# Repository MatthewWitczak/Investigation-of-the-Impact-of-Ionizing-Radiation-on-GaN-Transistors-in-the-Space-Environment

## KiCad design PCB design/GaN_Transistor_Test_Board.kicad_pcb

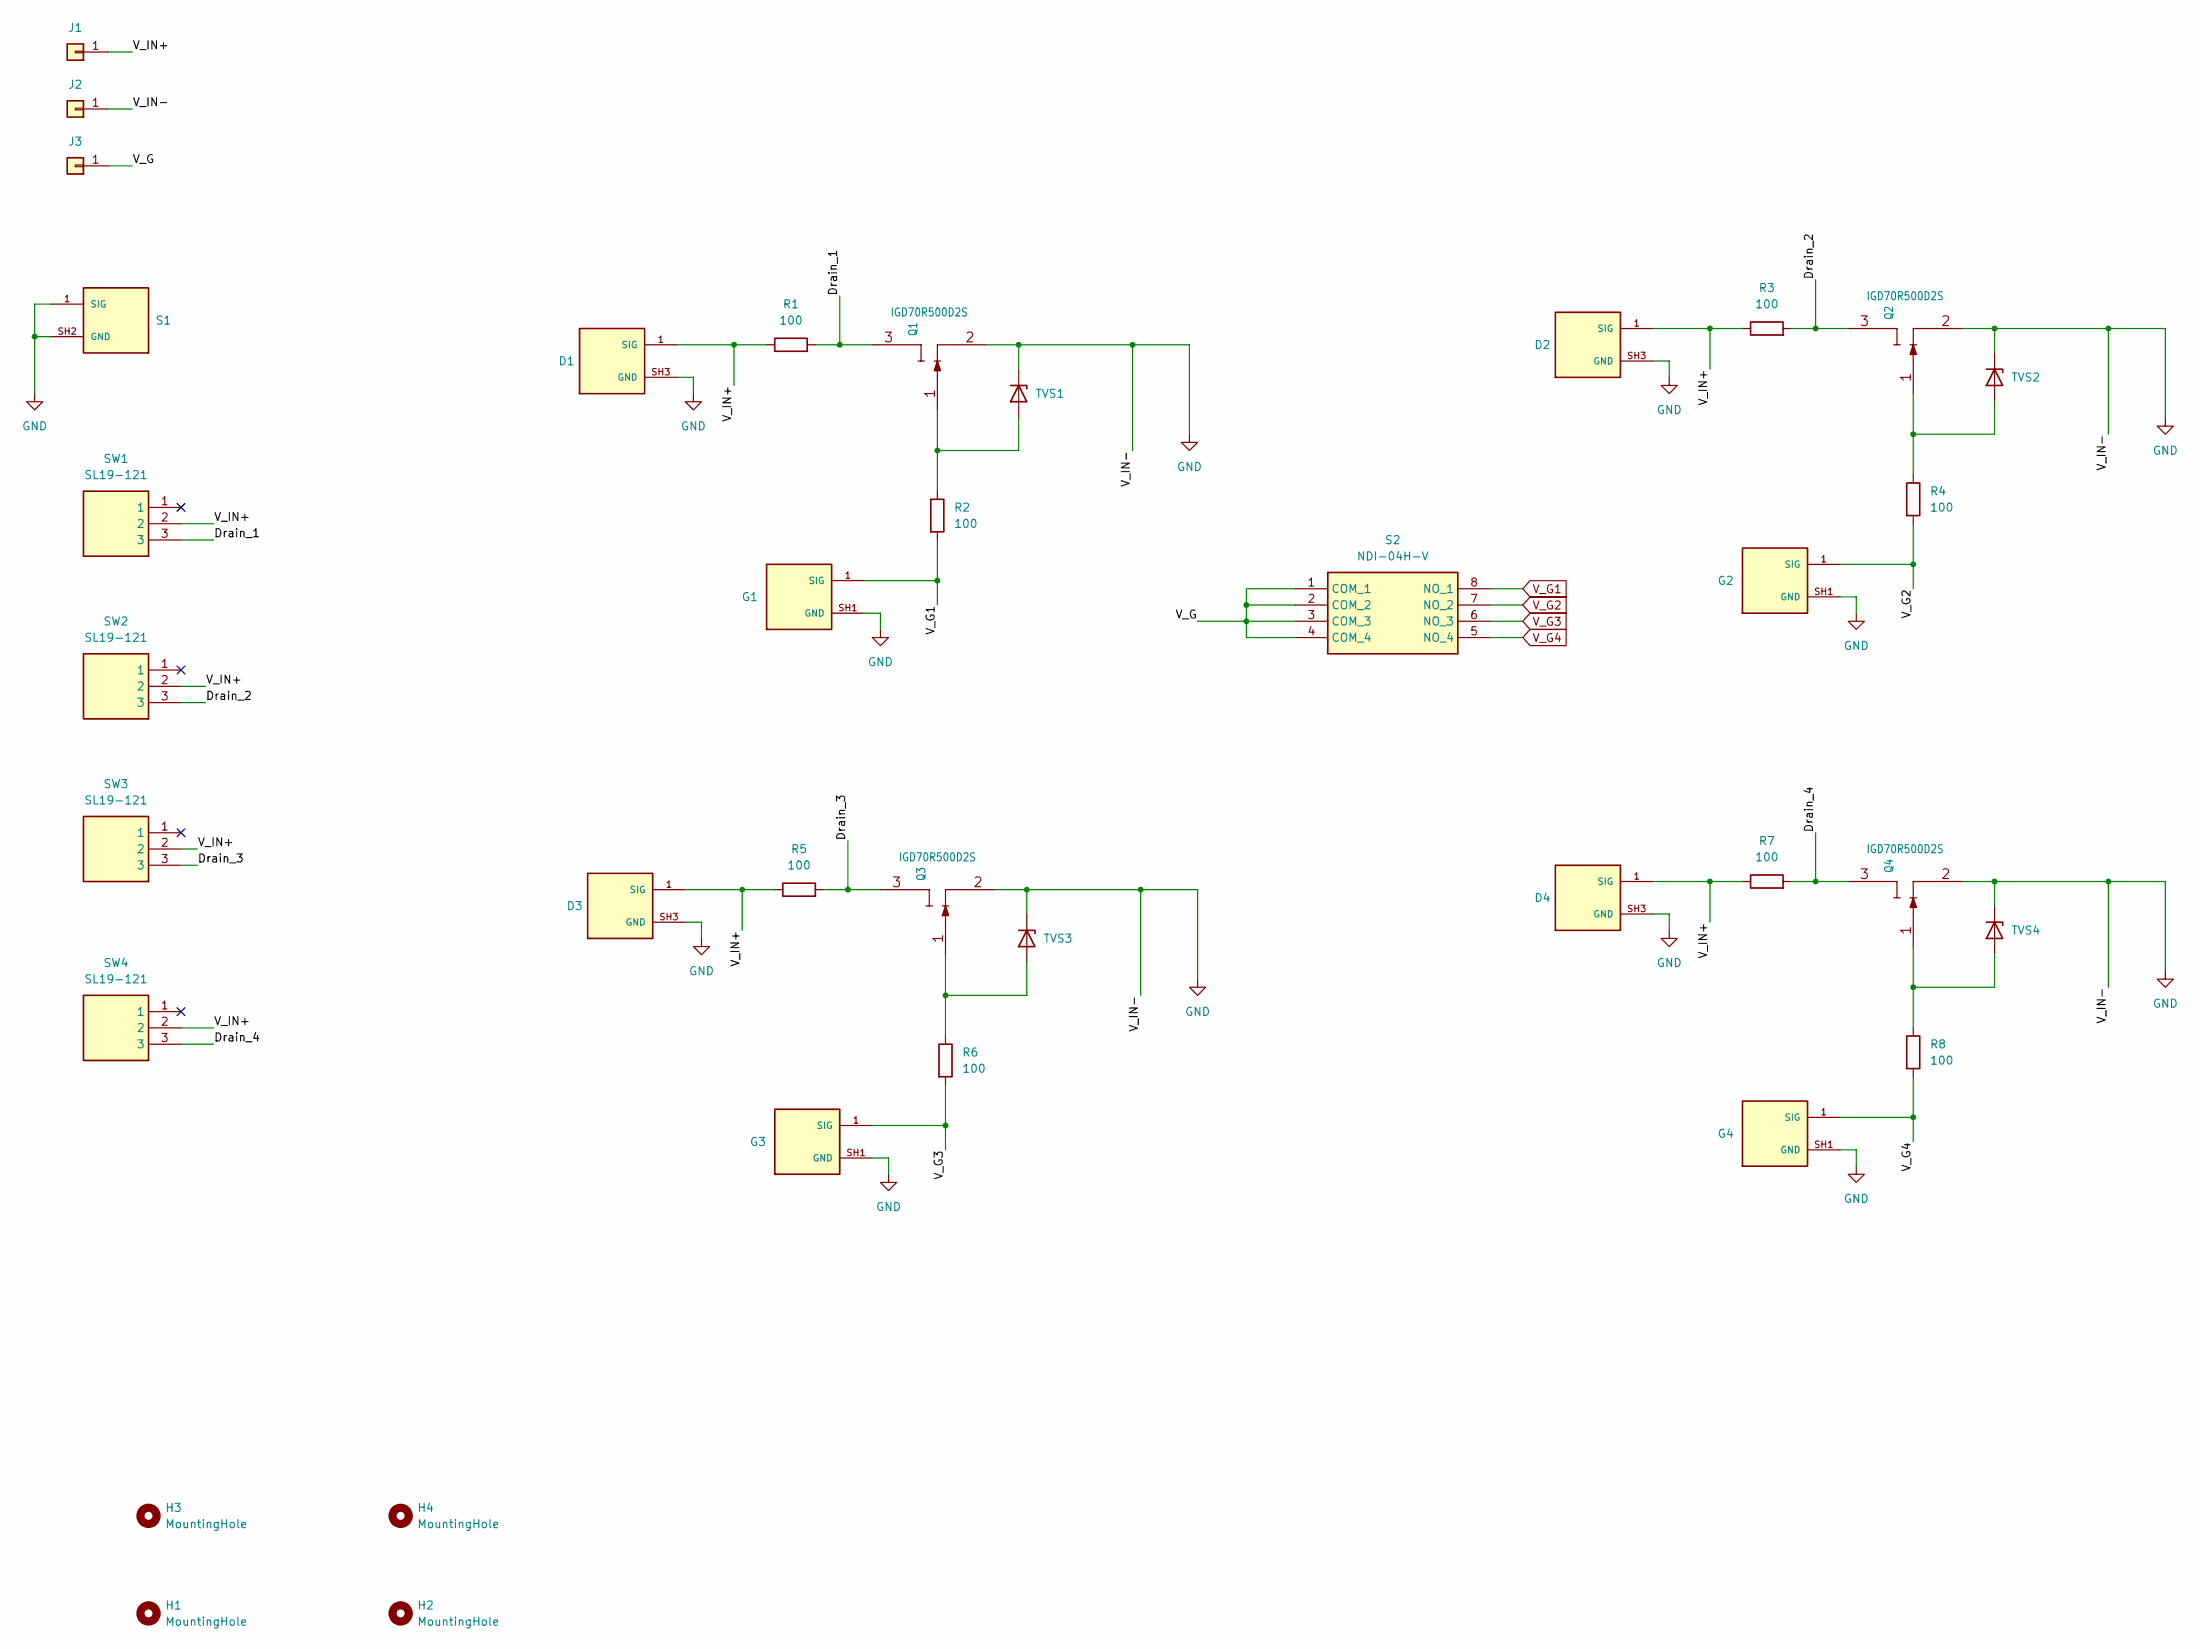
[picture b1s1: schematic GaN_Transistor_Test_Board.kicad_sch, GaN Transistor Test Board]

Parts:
D1, D2, D3, D4: 1-1337445-0; TE_1-1337445-0; PARTREV C
G1, G2, G3, G4: 1-1337445-0; TE_1-1337445-0; PARTREV C
H1, H2, H3, H4: MountingHole; MountingHole_4.3mm_M4
J1, J2, J3: Conn_01x01; CONN1_FCR7350R_CLF
Q1, Q2, Q3, Q4: IGD70R500D2S; IFX-PG-TO252-3N-37-V1
R1, R3, R5, R7: 100; R_LOAD
R2, R4, R6, R8: 100; R_1206_3216Metric_Pad1.30x1.75mm_HandSolder
S1: 1-1337445-0; TE_1-1337445-0; PARTREV C
S2: NDI-04H-V; NDI04HV; Manufacturer_Part_Number NDI-04H-V
SW1, SW2, SW3, SW4: SL19-121; SL19121; Manufacturer_Part_Number SL19-121
TVS1, TVS2, TVS3, TVS4: D_Zener; SMFSeries_LTF

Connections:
/Drain_1: Q1.3 (D), R1.2, SW1.3
/Drain_2: Q2.3 (D), R3.2, SW2.3
/Drain_3: Q3.3 (D), R5.2, SW3.3
/Drain_4: Q4.3 (D), R7.2, SW4.3
/V_G: J3.1, S2.1 (COM_1), S2.2 (COM_2), S2.3 (COM_3), S2.4 (COM_4)
/V_IN+: D1.1 (SIG), D2.1 (SIG), D3.1 (SIG), D4.1 (SIG), J1.1, R1.1, R3.1, R5.1, R7.1, SW1.2, SW2.2, SW3.2, SW4.2
GND: D1.SH3 (GND), D2.SH3 (GND), D3.SH3 (GND), D4.SH3 (GND), G1.SH1 (GND), G2.SH1 (GND), G3.SH1 (GND), G4.SH1 (GND), J2.1, Q1.2 (S), Q2.2 (S), Q3.2 (S), Q4.2 (S), S1.1 (SIG), S1.SH2 (GND), TVS1.1 (K), TVS2.1 (K), TVS3.1 (K), TVS4.1 (K)
unnamed: Q1.1 (G), R2.1, TVS1.2 (A)
unnamed: Q2.1 (G), R4.1, TVS2.2 (A)
unnamed: Q3.1 (G), R6.1, TVS3.2 (A)
unnamed: Q4.1 (G), R8.1, TVS4.2 (A)
V_G1: G1.1 (SIG), R2.2, S2.8 (NO_1)
V_G2: G2.1 (SIG), R4.2, S2.7 (NO_2)
V_G3: G3.1 (SIG), R6.2, S2.6 (NO_3)
V_G4: G4.1 (SIG), R8.2, S2.5 (NO_4)

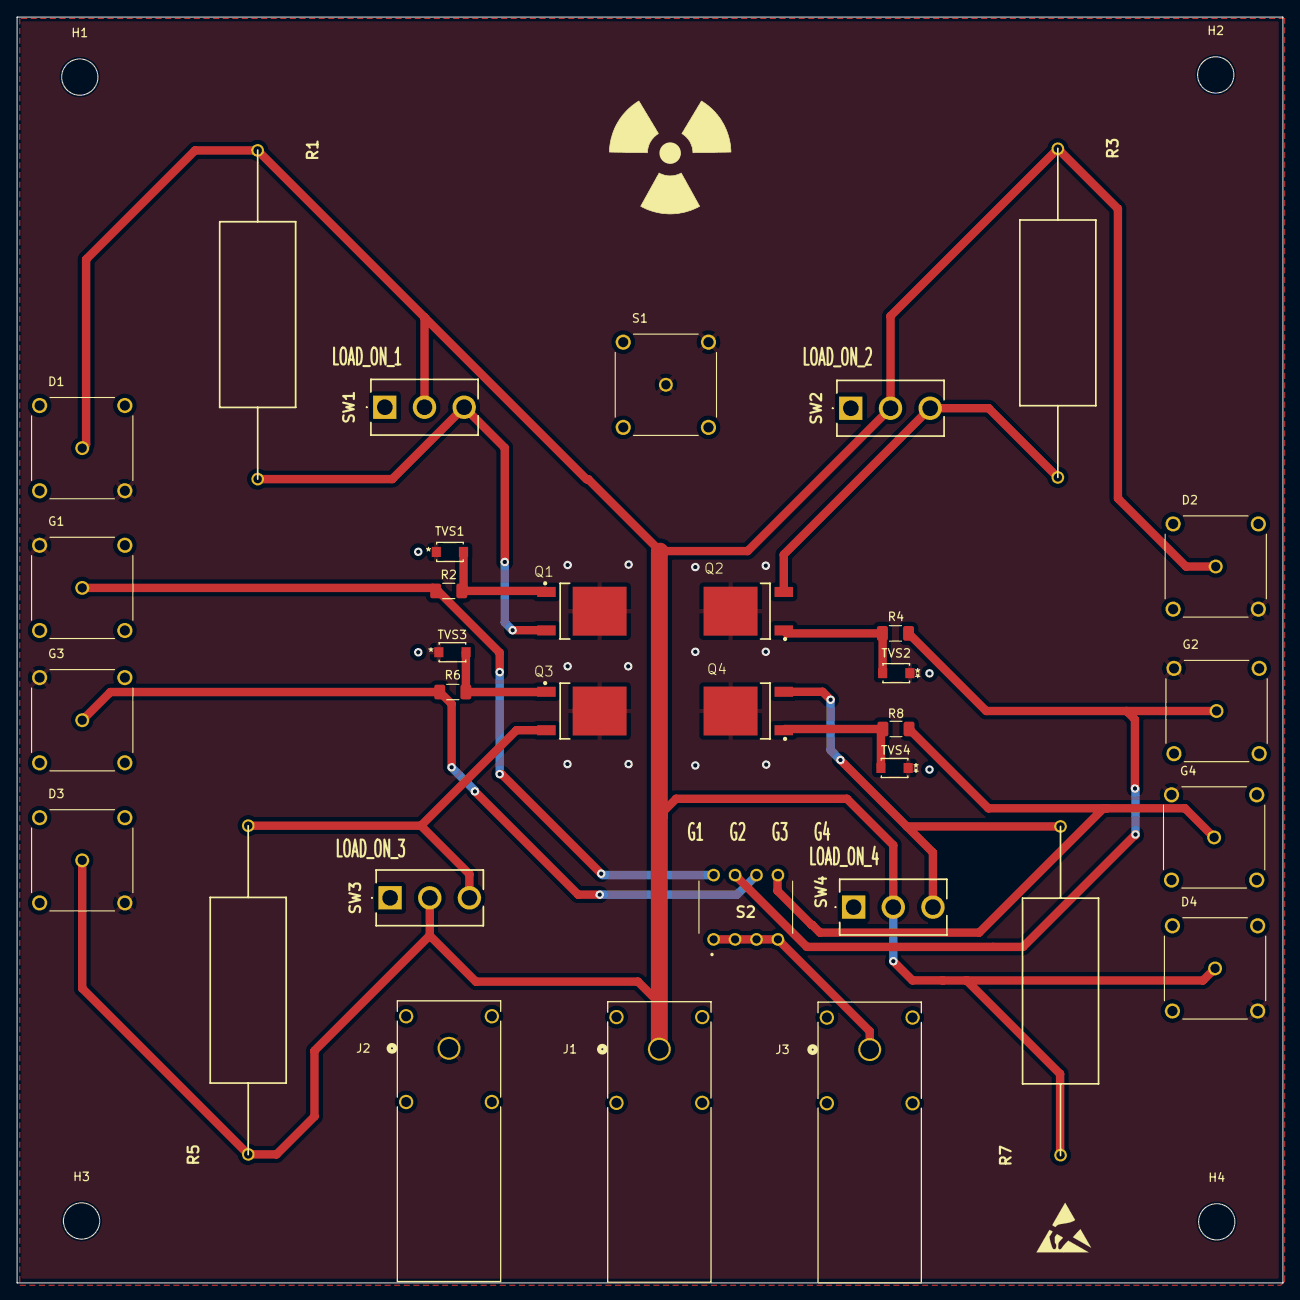
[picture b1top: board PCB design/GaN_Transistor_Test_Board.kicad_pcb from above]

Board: 2 copper layers, 150.0 x 150.0 mm, 37 parts (0 on the bottom side), 15 nets.

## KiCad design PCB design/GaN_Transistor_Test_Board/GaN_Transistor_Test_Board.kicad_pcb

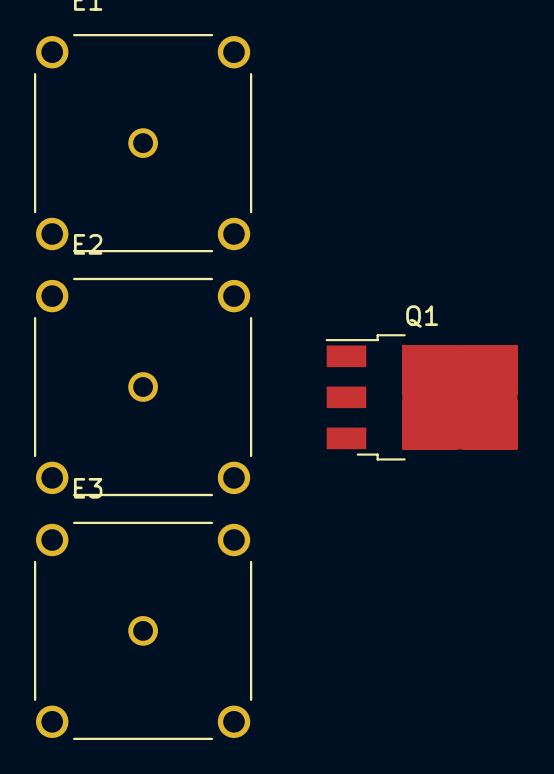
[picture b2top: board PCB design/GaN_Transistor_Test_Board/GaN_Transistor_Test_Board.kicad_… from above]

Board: 2 copper layers, 4 parts (0 on the bottom side), 4 nets, no tracks yet.

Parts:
E1, E2, E3: 1-1337445-0; TE_1-1337445-0
Q1: IGD70R500D2S; TO-252-3_TabPin4

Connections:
GND: E1.SH1 (GND), E2.SH2 (GND), E3.SH3 (GND)
unnamed: E1.1 (SIG), Q1.1 (G)
unnamed: E2.1 (SIG), Q1.2 (S)
unnamed: E3.1 (SIG), Q1.3 (D)

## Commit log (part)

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2025-12-29 Rename LTspice directory to Simulation
2026-01-18 Static characteristics simulation
2026-01-18 Add .gitignore
2026-01-18 Schematic
2026-01-18 PCB update V1
2026-01-18 Restructuring of the repository
2026-01-24 Layout redesign
2026-01-24 Add test points
2026-01-28 Simulation PCB update v1
